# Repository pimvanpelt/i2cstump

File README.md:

# Digistump I2C dongle

## Version 4 - USB Dongle

## Version 5 - USB-C Connector

## Hardware 

This device is an adaptation of [Digistump](http://digistump.com/products/1)'s
USB device, with two added [Qwiic](https://www.sparkfun.com/qwiic) connectors.
The first is used as a 5V I2C port, and the second has a level shifter to 3.3V
using [BSS138](https://www.onsemi.com/pub/Collateral/BSS138-D.PDF) FETs to
create a 3.3V I2C port. It's slightly bigger than the original, coming in 
at 34.0 x 18.7 mm (for the stump, which plugs directly into a USB port), or
25.9 x 18.8 mm (for the USB-C version)..

See my Oshpark projects: [v2](https://oshpark.com/shared_projects/iBBtdp7S),
[v3](https://oshpark.com/shared_projects/8I7qjXw7), 
[v4](https://oshpark.com/shared_projects/ChwKt4Mn),
[current-v5](https://oshpark.com/shared_projects/Jq9YXZ0q).

You can see a few pictures of the v3 board [here](https://photos.app.goo.gl/4XRo74y9Bt4kZoqR7).

### Bill of Materials

*   C1,C3: Tantalum 4.7 μF (0805)
*   C2: Ceramic 0.1 μF (0603)
*   D1,D2: 3.6V Zener (SOD-323)
*   D3: Blue (activity) LED (0603)
*   D4: Red (power) LED (0603)
*   IC1: ATTINY85 (SO08)
*   IC2:
    *   v2: AM1117 3.3V (SOT223)
    *   v3+: MCP1703 3.3V (SOT23)
*   J1,J2: QWIIC Connector (1X04 1MM RA)
*   Q1,Q2: BSS138 (SOT23-3)
*   R1,R2: 66 Ω (0603)
*   R3,R7: 680 Ω (0603)
*   R4: 2.2 kΩ (0603)
*   R5,R6: 5.1 kΩ (0603)
*   RN1: 10 kΩ (0805)
*   USB-C 16 pin connector

To build this board by hand, take a look at the [instructions](BUILDING.md).

## Firmware

The ATTiny85 is first flashed with [Micronucleus](https://github.com/micronucleus/micronucleus),
a bootloader which equips the microcontroller with a minimal USB interface. You can use the
`ICSP` touchpoint header at the bottom of the board to flash.

Firmware which runs under the micronucleus bootloader is [I2C-Tiny-USB](https://github.com/harbaum/I2C-Tiny-USB)
which is detected under Linux using the [i2c-tiny-usb](https://github.com/torvalds/linux/blob/master/drivers/i2c/busses/i2c-tiny-usb.c)
driver.

## Acknowledgements

Thanks go to:

*   Digistump LLC for sharing the original for this device under Creative Commons.
*   Tim Böscke, Jenna Fox, Shay Green et al for the Micronucleus bootloader.
*   Till Harbaum for an excellent ATTINY85 firmware for an I2C bridge.

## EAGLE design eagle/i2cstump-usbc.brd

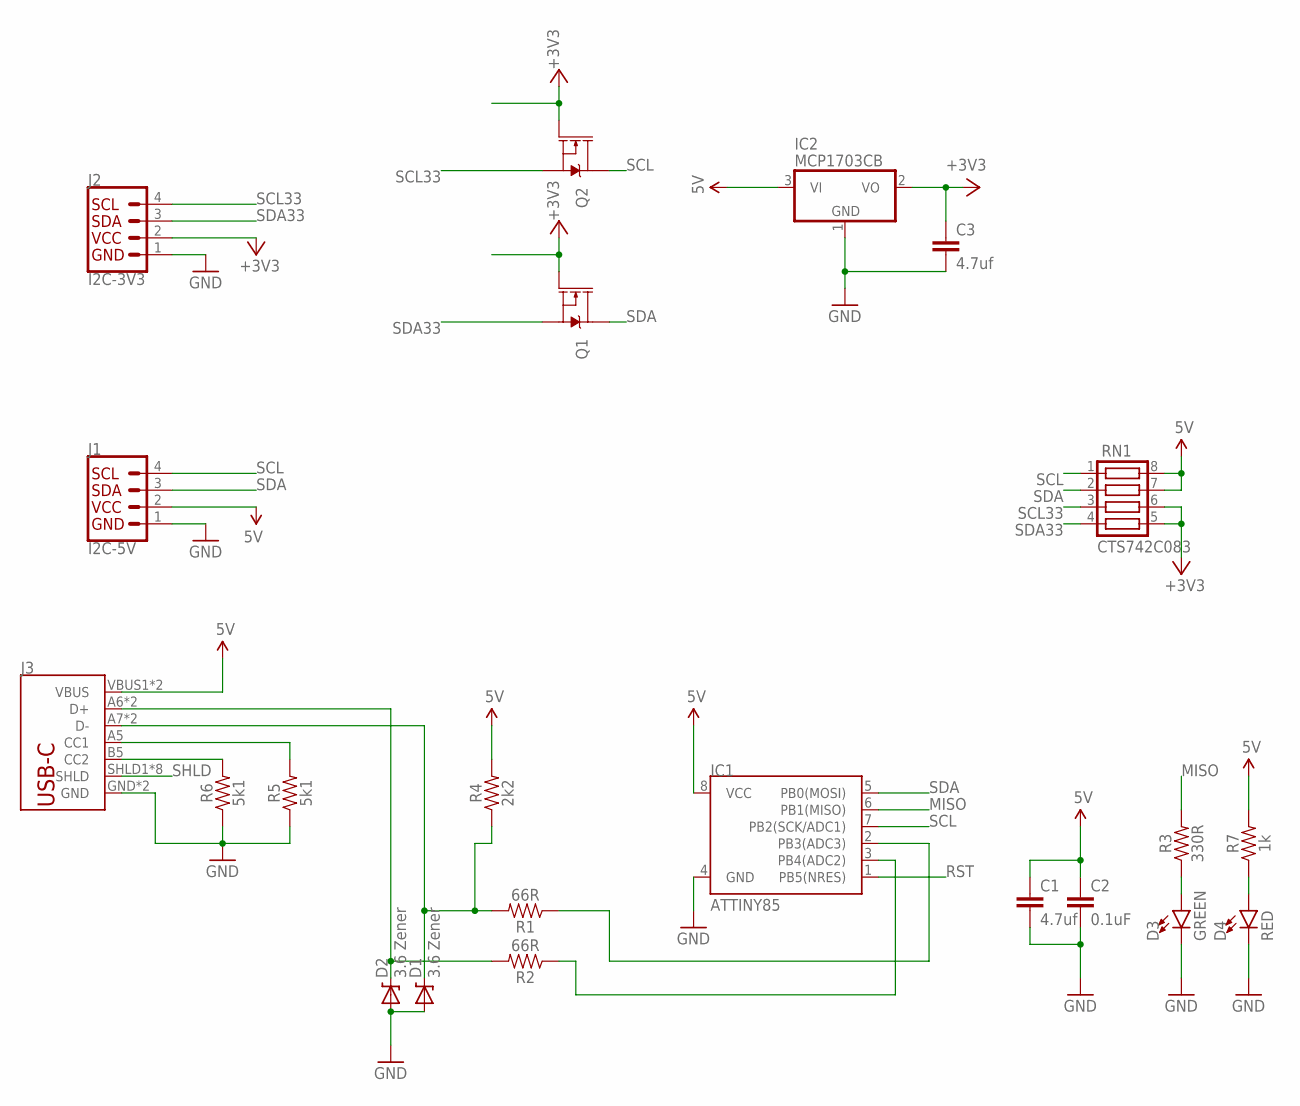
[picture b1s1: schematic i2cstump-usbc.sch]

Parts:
C1, C3: 4.7uf; 0805
C2: 0.1uF; 0603
D1, D2: 3.6 Zener; SOD-323
D3: GREEN; LED-0603
D4: RED; LED-0603
IC1: ATTINY85; SO08-EIAJ
IC2: MCP1703CB; SOT23
J1: I2C-5V; 1X04_1MM_RA
J2: I2C-3V3; 1X04_1MM_RA
J3: USB_C16PIN; USB-C-16P
Q1, Q2: 220mA/50V/3.5Ω; SOT23-3
R1, R2: 66R; 0603
R3: 330R; 0603
R4: 2k2; 0603
R5, R6: 5k1; 0603
R7: 1k; 0603
RN1: CTS742C083

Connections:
5V: C1.1, C2.1, IC1.8 (VCC), IC2.3 (VI), J1.2 (VCC), J3.VBUS1 (VBUS), J3.VBUS2 (VBUS), R4.2, R7.2, RN1.7, RN1.8
+3V3: C3.1, IC2.2 (VO), J2.2 (VCC), Q1.1 (G), Q2.1 (G), RN1.5, RN1.6
GND: C1.2, C2.2, C3.2, D1.2 (A), D2.2 (A), D3.C, D4.C, IC1.4 (GND), IC2.1 (GND), J1.1 (GND), J2.1 (GND), J3.GND, J3.GND2 (GND), R5.1, R6.1
MISO: IC1.6 (PB1(MISO)), R3.2
unnamed: IC1.2 (PB3(ADC3)), R1.1
unnamed: D3.A, R3.1
unnamed: D4.A, R7.1
unnamed: J3.A5 (CC1), R5.2
unnamed: J3.B5 (CC2), R6.2
unnamed: IC1.3 (PB4(ADC2)), R2.1
RST: IC1.1 (PB5(NRES))
SCL: IC1.7 (PB2(SCK/ADC1)), J1.4 (SCL), Q2.3 (D), RN1.1
SCL33: J2.4 (SCL), Q2.2 (S), RN1.3
SDA: IC1.5 (PB0(MOSI)), J1.3 (SDA), Q1.3 (D), RN1.2
SDA33: J2.3 (SDA), Q1.2 (S), RN1.4
SHLD: J3.SHLD1 (SHLD), J3.SHLD2 (SHLD), J3.SHLD3 (SHLD), J3.SHLD4 (SHLD), J3.SHLD5 (SHLD), J3.SHLD6 (SHLD), J3.SHLD7 (SHLD), J3.SHLD8 (SHLD)
USB_M: D1.1 (C), J3.A7 (D-), J3.B7 (D-), R1.2, R4.1
USB_P: D2.1 (C), J3.A6 (D+), J3.B6 (D+), R2.2

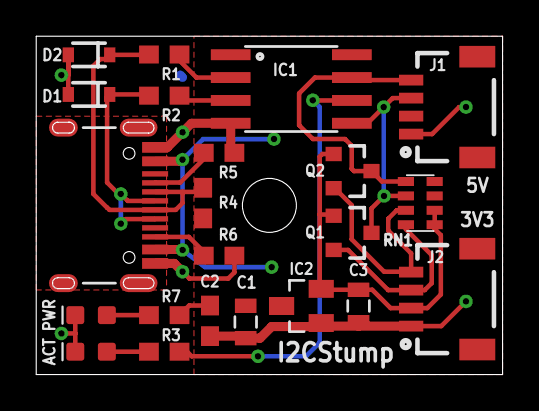
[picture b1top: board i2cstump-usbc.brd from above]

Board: 2 copper layers, 25.9 x 18.8 mm, 22 parts (0 on the bottom side), 17 nets.

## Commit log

2018-12-29 V1.0 -- ordered @oshpark
2018-12-29 Remove text from Digispark -- will attribute in README.md
2018-12-29 Add README - plus thanks to the original authors.
2018-12-29 Resize image to 154x90
2018-12-29 Update with BOM
2018-12-29 Fix typos
2018-12-29 Clean up schematic -- split out the levelshifter from the 5V pullups
2018-12-29 Cleanup BRD -- remove stubs, remove redundant 5V traces (they are on the top plane), widen 5V and GND traces to 0.02
2018-12-29 Update image -- use eagle render
2018-12-29 Add back groundplane to image
2018-12-29 Add some more GND via's - name USB_M and USB_P; Move AM1117 a bit so that 5V has more copper on ingress
2018-12-29 Move AM1117 a bit to the left again, as it was really close to C3
2018-12-29 Update picture
2018-12-29 Add C3 to BOM
2018-12-31 Version 2.0
    Now with ICSP touchpoints at the bottom so I can flash the AVR.
    Also placed tantalum cap C3 (4.uF) on the output of the AM1117.
2018-12-31 Add Oshpark link
2018-12-31 Add micronucleus note
2018-12-31 Add acknowledgement to Micronucleus authors
2018-12-31 Version 3.0 -- with 3mm screwhole in the center. Aligned J1/J2 to be 0.76mm from the edges. Replaced bulky AM1117 (SOT223) with a MCP1700 (SOT23)
2018-12-31 Add v3 with a SOT23 smaller LDO
2018-12-31 Add v2 and v3 links to oshpark
2018-12-31 Add datasheets
2018-12-31 Add a building howto.
2018-12-31 Change R3 to 390R, 2.2V green LED, not too bright
2019-01-01 Move D1,D2,C3 silk around; center other silk
2019-01-01 Add fusecalc link
2019-07-01 Move R4 to align with C1/C2
2019-07-02 Add Photos
2019-07-07 s/Digispark/I2CStump/
2019-07-08 Version 4.0
    Changes:
    - swap out PWR led for ACT led on MISO pin (the USB Tiny I2C firmware
    blinks MISO on I2C activity.
    - swap out 10KOhm pullup resistors for an 0805 resistor network RN1.
2019-07-08 Update v4 to be RN1 for I2C pullups
2019-07-08 Bump to v4
2019-07-08 Add link to oshparh for v4
2019-07-20 Version 5 of the board - USB-C!
2019-07-20 Add a few mm of length to the USB stump
2019-07-20 Reference proper dimensions of the v4 and v5 board
2019-07-20 Correct geometry of the v5 board (it was off-by-5mils)
2019-07-20 Center the USB-C connector
2019-07-20 Move hole to center of board
2019-08-15 Correct value of R7 (390R)
2019-08-16 Change red PWR led to be 1k resistor so it's not as bright. Conversely, lower green ACT led to 330R so it's a bit brighter

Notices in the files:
parts and their libraries:
SparkFun: Licensing: CC v3.0 Share-Alike You are welcome to use this library for commercial purposes.
SparkFun-Connectors: Licensing: Creative Commons ShareAlike 4.0 International - https://creativecommons.org/licenses/by-sa/4.0
